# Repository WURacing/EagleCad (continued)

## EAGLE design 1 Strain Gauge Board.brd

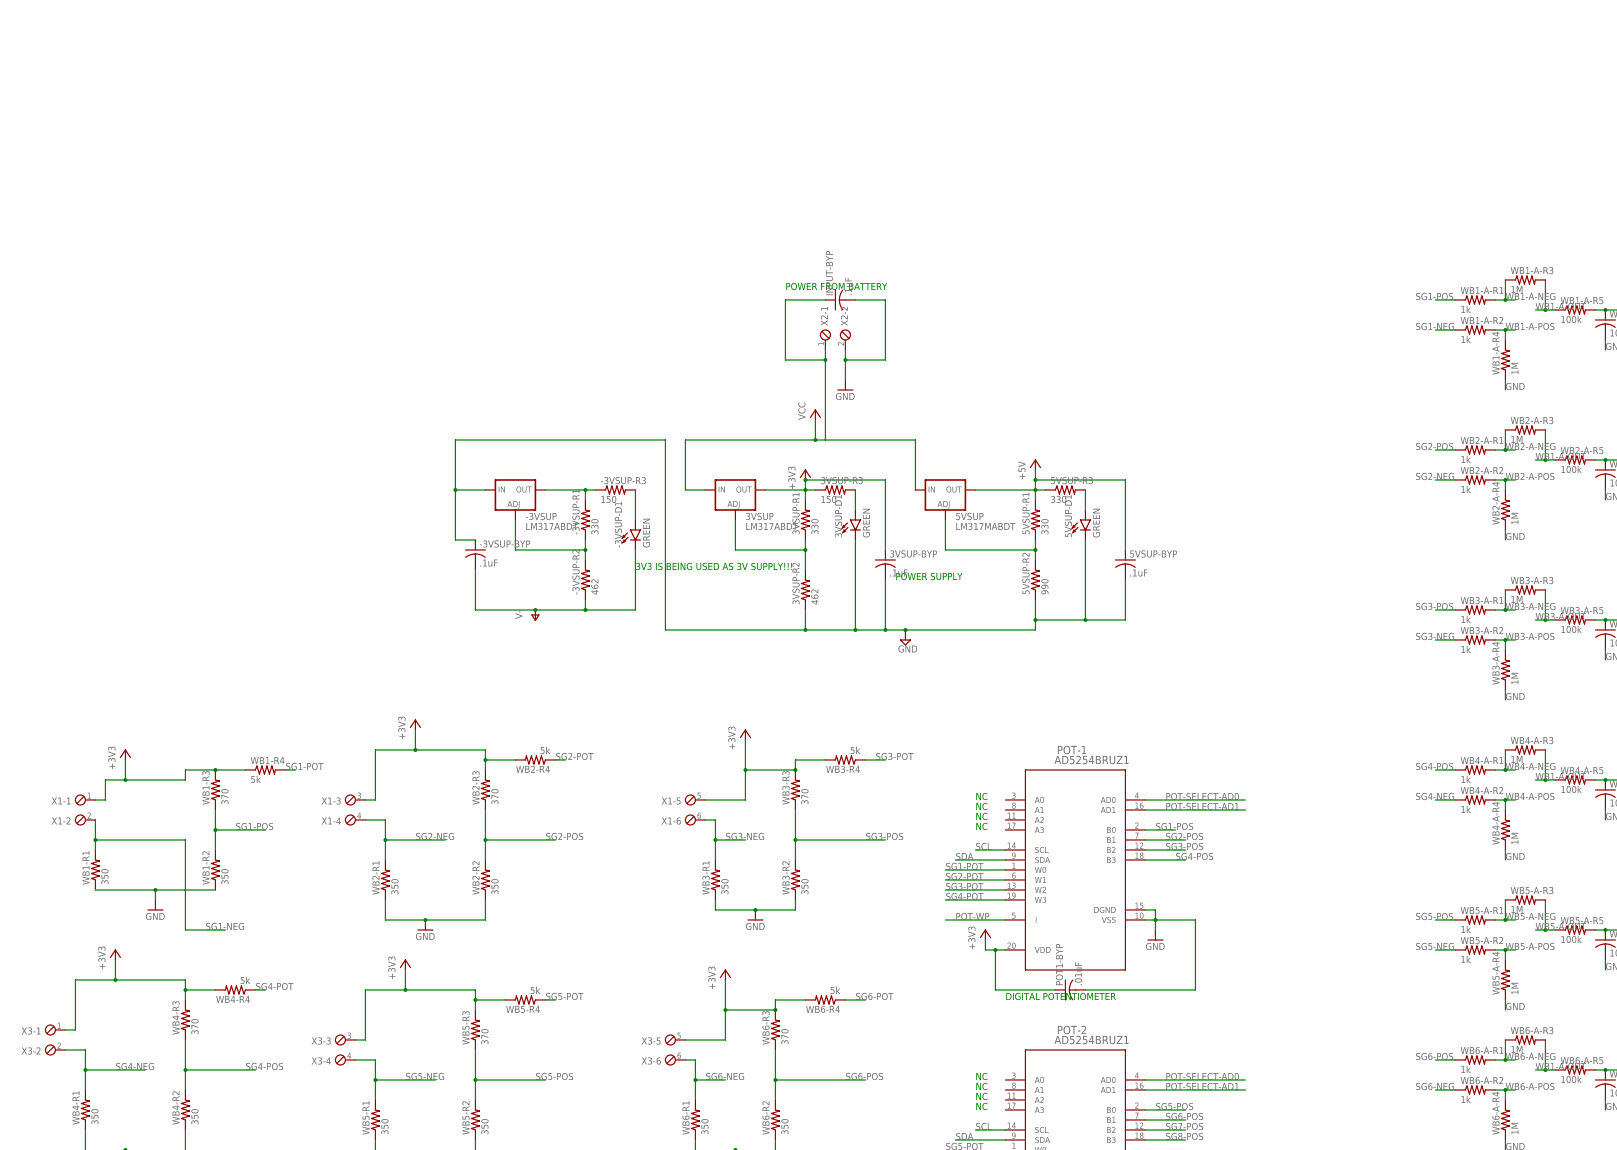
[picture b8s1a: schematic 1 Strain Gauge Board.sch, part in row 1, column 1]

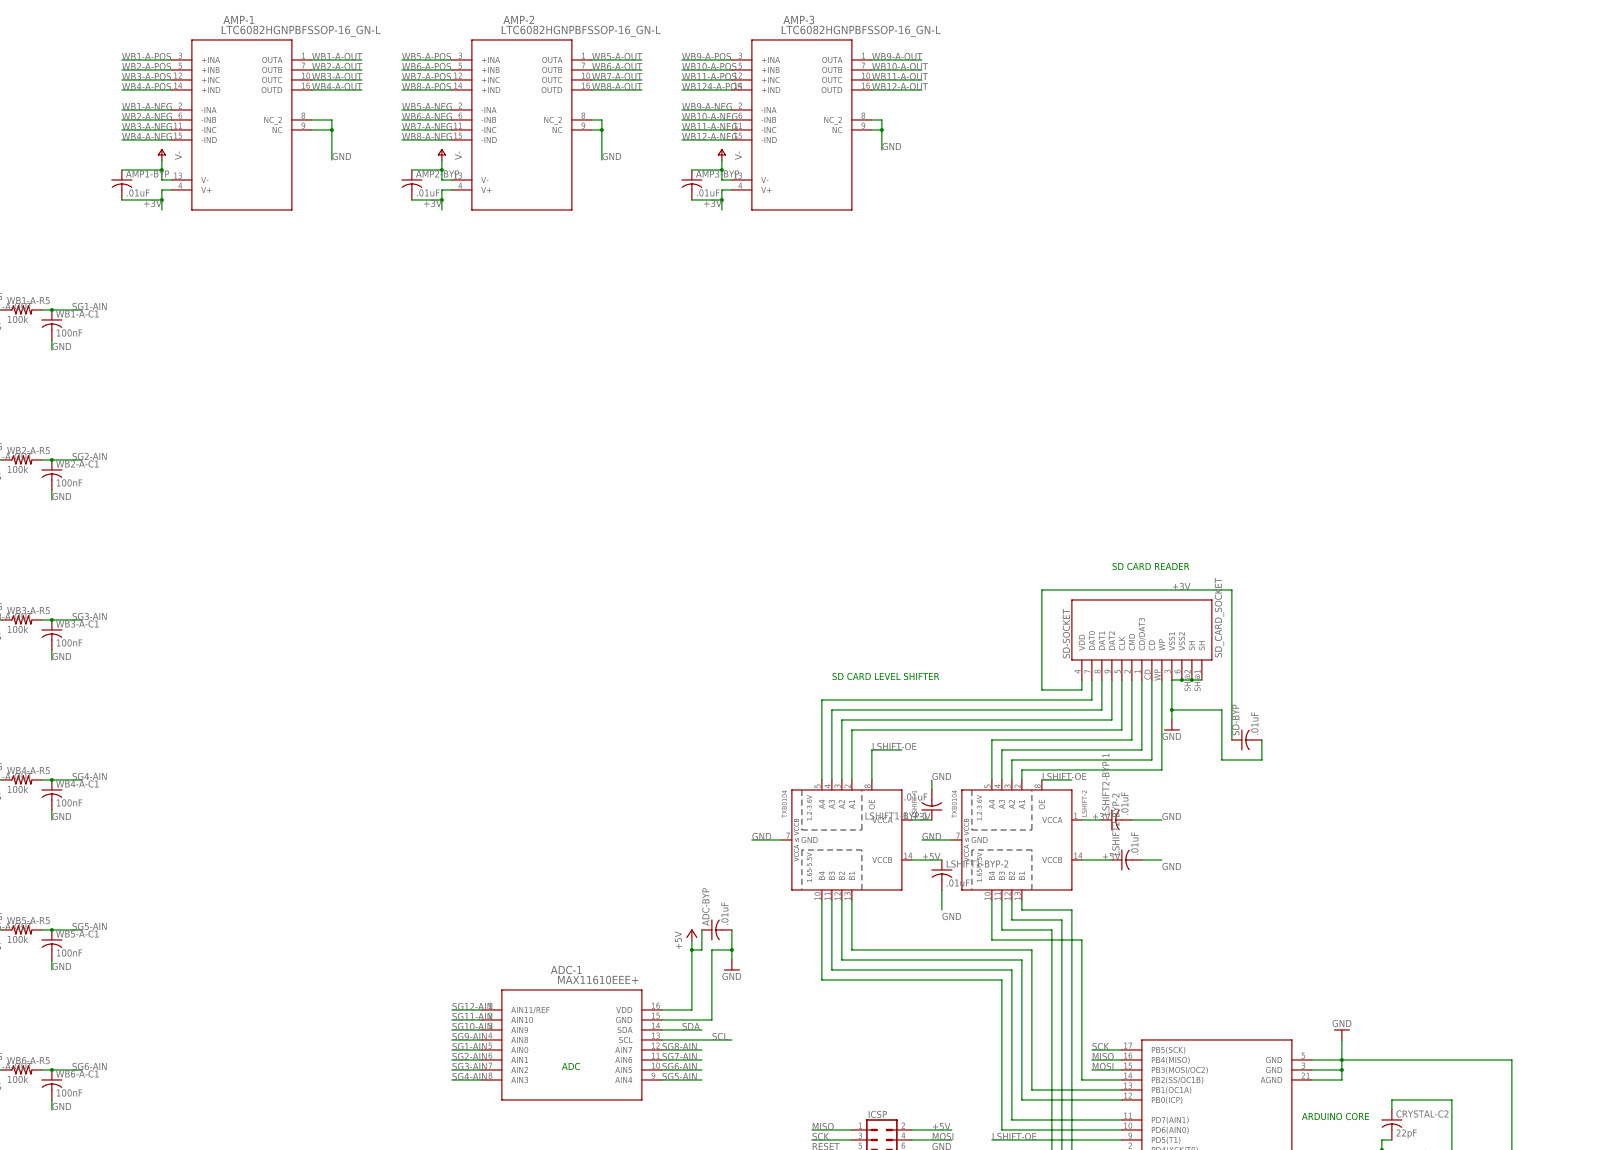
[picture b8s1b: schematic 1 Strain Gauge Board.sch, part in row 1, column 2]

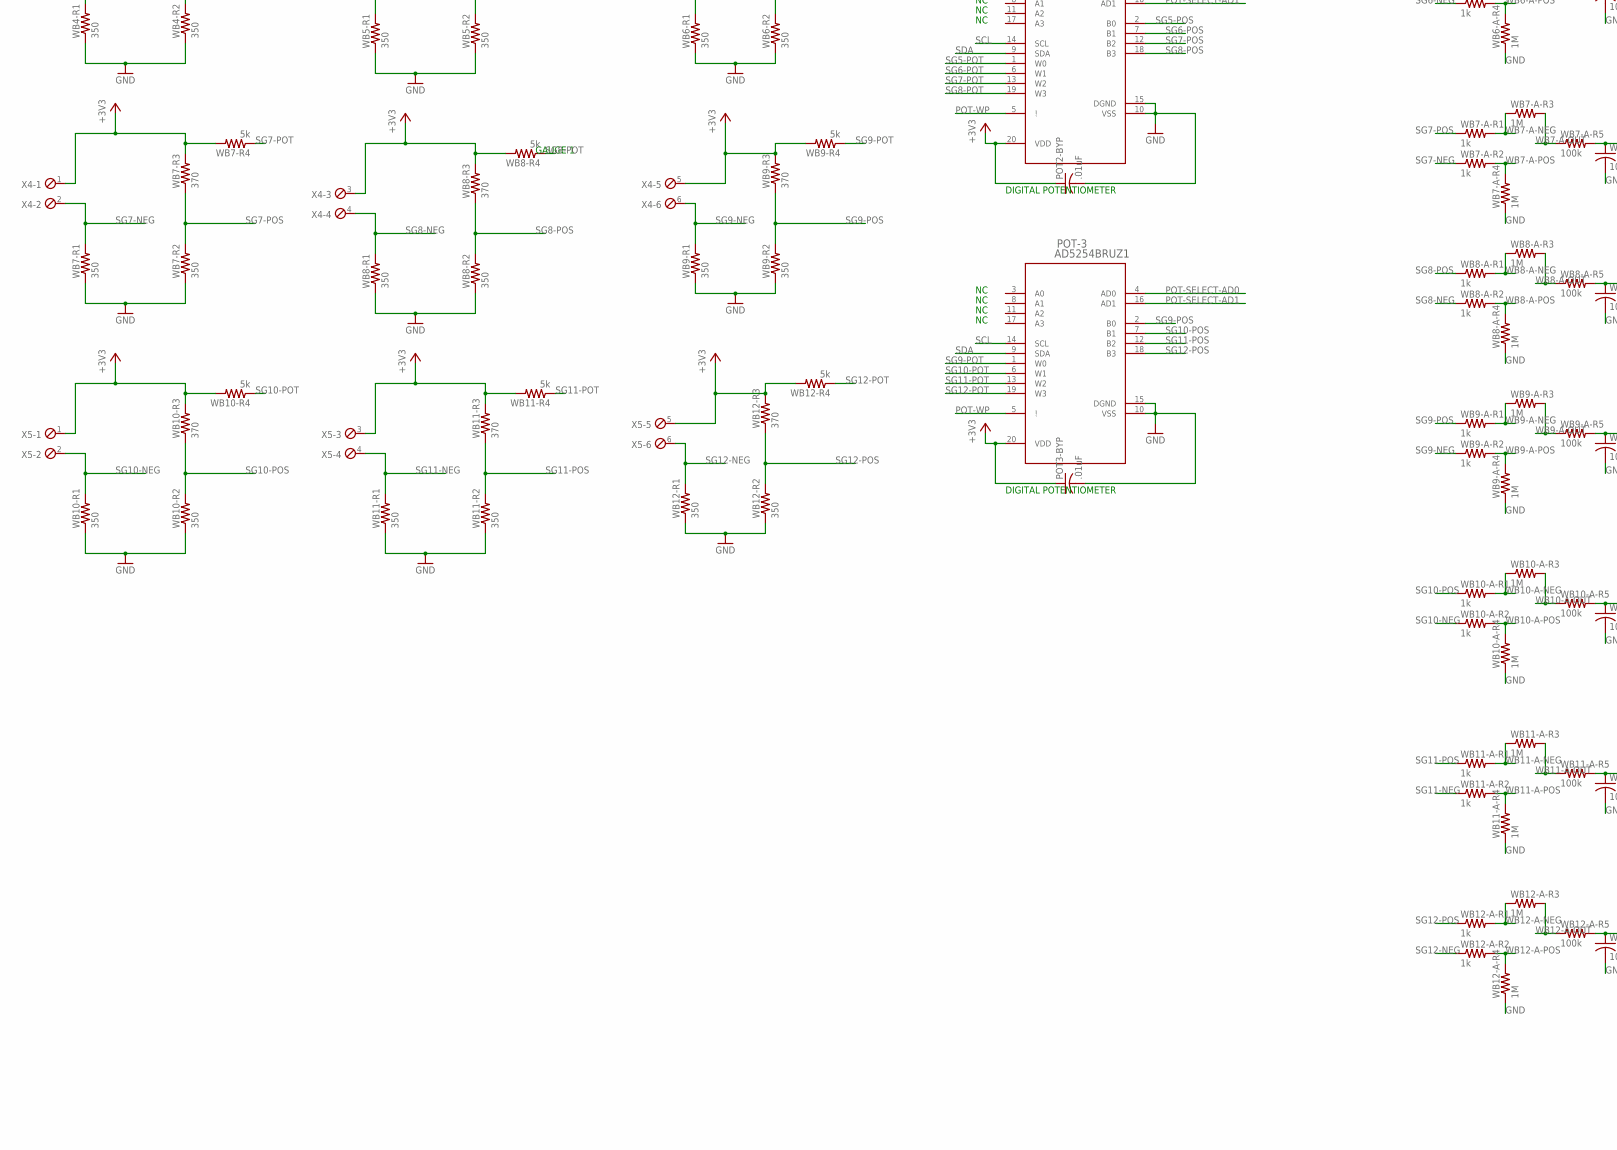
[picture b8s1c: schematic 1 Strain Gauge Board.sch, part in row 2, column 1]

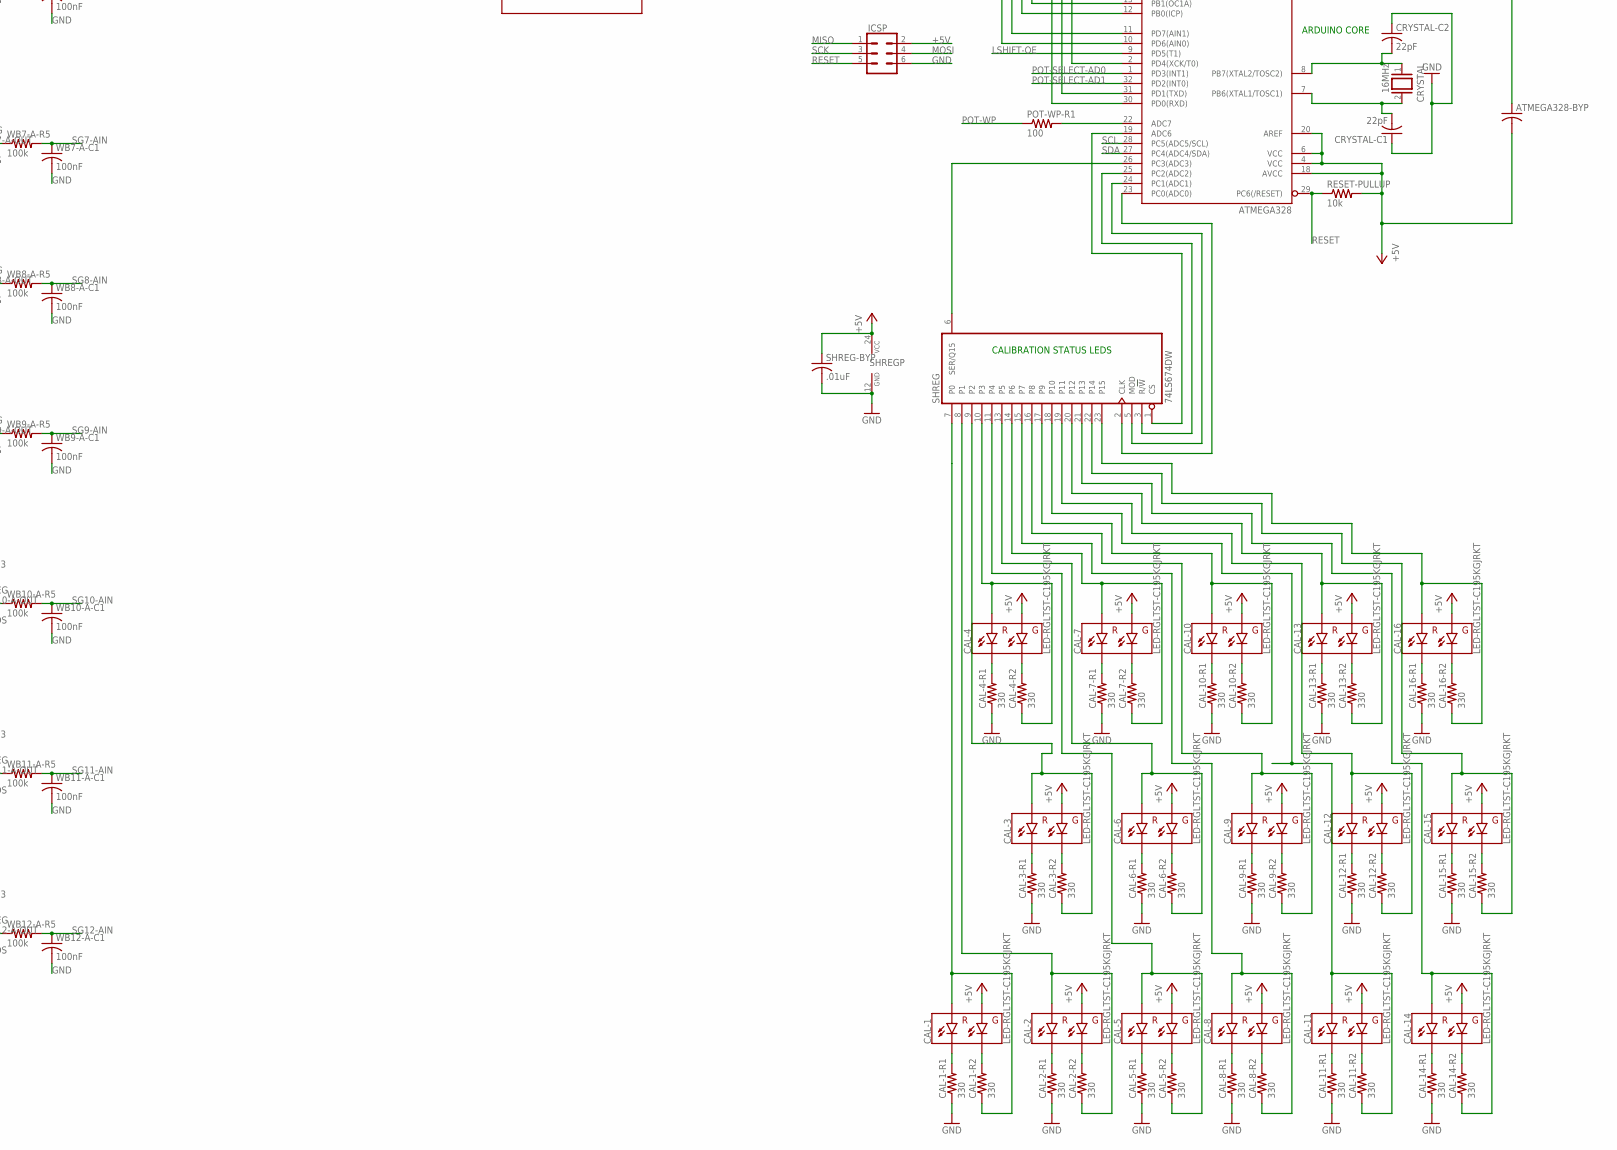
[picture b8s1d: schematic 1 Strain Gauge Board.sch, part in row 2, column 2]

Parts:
3VSUP: LM317ABDT; DPACK
3VSUP-BYP, 5VSUP-BYP: .1uF; C1206K
3VSUP-D1, 5VSUP-D1: GREEN; LED-1206
3VSUP-R1, 5VSUP-R1, 5VSUP-R3: 330; M1206
3VSUP-R2: 462; M1206
3VSUP-R3: 150; M1206
5VSUP: LM317MABDT; DPACK
5VSUP-R2: 990; M1206
-3VSUP: LM317ABDT; DPACK
-3VSUP-BYP: .1uF; C1206K
-3VSUP-D1: GREEN; LED-1206
-3VSUP-R1: 330; M1206
-3VSUP-R2: 462; M1206
-3VSUP-R3: 150; M1206
ADC-1: MAX11610EEE+; 21-0055H_16
ADC-BYP: .01uF; C1206K
AMP1-BYP, AMP2-BYP, AMP3-BYP: .01uF; C1206K
AMP-1, AMP-2, AMP-3: LTC6082HGNPBFSSOP-16_GN-L; SSOP-16_GN-L
ATMEGA328: ATMEGA328P_TQFP; TQFP32-08
ATMEGA328-BYP: C-USC1206; C1206
CAL-1, CAL-2, CAL-3, CAL-4, CAL-5, CAL-6, CAL-7, CAL-8, CAL-9, CAL-10, CAL-11, CAL-12, CAL-13, CAL-14, CAL-15, CAL-16: LED-RGLTST-C195KGJRKT; LTST-C195KGJRKT
CAL-1-R1, CAL-1-R2, CAL-2-R1, CAL-2-R2, CAL-3-R1, CAL-3-R2, CAL-4-R1, CAL-4-R2, CAL-5-R1, CAL-5-R2, CAL-6-R1, CAL-6-R2, CAL-7-R1, CAL-7-R2, CAL-8-R1, CAL-8-R2, CAL-9-R1, CAL-9-R2, CAL-10-R1, CAL-10-R2, CAL-11-R1, CAL-11-R2, CAL-12-R1, CAL-12-R2, CAL-13-R1, CAL-13-R2, CAL-14-R1, CAL-14-R2, CAL-15-R1, CAL-15-R2, CAL-16-R1, CAL-16-R2: 330; M1206
CRYSTAL: 16MHz; QS
CRYSTAL-C1, CRYSTAL-C2: 22pF; C1206K
ICSP: CONN_03X2FEMALE; 2X3
INPUT-BYP: .1uF; C1206K
LSHIFT1-BYP-1, LSHIFT1-BYP-2, LSHIFT2-BYP-1, LSHIFT2-BYP-2: .01uF; C1206K
LSHIFT-1, LSHIFT-2: TXB0104; SO14
POT1-BYP, POT2-BYP, POT3-BYP: .01uF; C1206K
POT-1, POT-2, POT-3: AD5254BRUZ1; RU_20
POT-WP-R1: 100; M1206
RESET-PULLUP: 10k; M1206
SD-BYP: .01uF; C1206K
SD-SOCKET: SD_CARD_SOCKET; SD
SHREG: 74LS674DW; SO24W
SHREG-BYP: .01uF; C1206K
WB1-A-C1, WB2-A-C1, WB3-A-C1, WB4-A-C1, WB5-A-C1, WB6-A-C1, WB7-A-C1, WB8-A-C1, WB9-A-C1, WB10-A-C1, WB11-A-C1, WB12-A-C1: 100nF; C1206K
WB1-A-R1, WB1-A-R2, WB2-A-R1, WB2-A-R2, WB3-A-R1, WB3-A-R2, WB4-A-R1, WB4-A-R2, WB5-A-R1, WB5-A-R2, WB6-A-R1, WB6-A-R2, WB7-A-R1, WB7-A-R2, WB8-A-R1, WB8-A-R2, WB9-A-R1, WB9-A-R2, WB10-A-R1, WB10-A-R2, WB11-A-R1, WB11-A-R2, WB12-A-R1, WB12-A-R2: 1k; M1206
WB1-A-R3, WB1-A-R4, WB2-A-R3, WB2-A-R4, WB3-A-R3, WB3-A-R4, WB4-A-R3, WB4-A-R4, WB5-A-R3, WB5-A-R4, WB6-A-R3, WB6-A-R4, WB7-A-R3, WB7-A-R4, WB8-A-R3, WB8-A-R4, WB9-A-R3, WB9-A-R4, WB10-A-R3, WB10-A-R4, WB11-A-R3, WB11-A-R4, WB12-A-R3, WB12-A-R4: 1M; M1206
WB1-A-R5, WB2-A-R5, WB3-A-R5, WB4-A-R5, WB5-A-R5, WB6-A-R5, WB7-A-R5, WB8-A-R5, WB9-A-R5, WB10-A-R5, WB11-A-R5, WB12-A-R5: 100k; M1206
WB1-R1, WB1-R2, WB2-R1, WB2-R2, WB3-R1, WB3-R2, WB4-R1, WB4-R2, WB5-R1, WB5-R2, WB6-R1, WB6-R2, WB7-R1, WB7-R2, WB8-R1, WB8-R2, WB9-R1, WB9-R2, WB10-R1, WB10-R2, WB11-R1, WB11-R2, WB12-R1, WB12-R2: 350; M1206
WB1-R3, WB2-R3, WB3-R3, WB4-R3, WB5-R3, WB6-R3, WB7-R3, WB8-R3, WB9-R3, WB10-R3, WB11-R3, WB12-R3: 370; M1206
WB1-R4, WB2-R4, WB3-R4, WB4-R4, WB5-R4, WB6-R4, WB7-R4, WB8-R4, WB9-R4, WB10-R4, WB11-R4, WB12-R4: 5k; M1206
X1, X3, X4, X5: MPT6; 6POL254
X2: MPT2; 2POL254

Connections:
+3V: 3VSUP.4 (OUT), 3VSUP-BYP.1, 3VSUP-R1.2, 3VSUP-R3.1, AMP1-BYP.2, AMP2-BYP.2, AMP3-BYP.2, AMP-1.4 (V+), AMP-2.4 (V+), AMP-3.4 (V+), LSHIFT1-BYP-1.1, LSHIFT2-BYP-1.1, LSHIFT-1.1 (VCCA), LSHIFT-2.1 (VCCA), POT1-BYP.1, POT2-BYP.1, POT3-BYP.1, POT-1.20 (VDD), POT-2.20 (VDD), POT-3.20 (VDD), SD-BYP.1, SD-SOCKET.4 (VDD), WB1-R3.2, WB1-R4.1, WB2-R3.2, WB2-R4.2, WB3-R3.2, WB3-R4.2, WB4-R3.2, WB4-R4.2, WB5-R3.2, WB5-R4.2, WB6-R3.2, WB6-R4.2, WB7-R3.2, WB7-R4.2, WB8-R3.2, WB8-R4.2, WB9-R3.2, WB9-R4.2, WB10-R3.2, WB10-R4.2, WB11-R3.2, WB11-R4.2, WB12-R3.2, WB12-R4.2, X1.1, X1.3, X1.5, X3.1, X3.3, X3.5, X4.1, X4.3, X4.5, X5.1, X5.3, X5.5
+5V: 5VSUP.4 (OUT), 5VSUP-BYP.1, 5VSUP-R1.2, 5VSUP-R3.1, ADC-1.16 (VDD), ADC-BYP.1, ATMEGA328.4 (VCC), ATMEGA328.6 (VCC), ATMEGA328.18 (AVCC), ATMEGA328.20 (AREF), ATMEGA328-BYP.2, CAL-1.P$1 (GA), CAL-2.P$1 (GA), CAL-3.P$1 (GA), CAL-4.P$1 (GA), CAL-5.P$1 (GA), CAL-6.P$1 (GA), CAL-7.P$1 (GA), CAL-8.P$1 (GA), CAL-9.P$1 (GA), CAL-10.P$1 (GA), CAL-11.P$1 (GA), CAL-12.P$1 (GA), CAL-13.P$1 (GA), CAL-14.P$1 (GA), CAL-15.P$1 (GA), CAL-16.P$1 (GA), ICSP.2, LSHIFT1-BYP-2.1, LSHIFT2-BYP-2.1, LSHIFT-1.14 (VCCB), LSHIFT-2.14 (VCCB), RESET-PULLUP.2, SHREG.24 (VCC), SHREG-BYP.1
-3V: -3VSUP.4 (OUT), -3VSUP-R1.2, -3VSUP-R3.1
GND: 3VSUP-BYP.2, 3VSUP-D1.C, 3VSUP-R2.1, 5VSUP-BYP.2, 5VSUP-D1.C, 5VSUP-R2.1, -3VSUP.3 (IN), -3VSUP-BYP.1, ADC-1.15 (GND), ADC-BYP.2, AMP-1.8 (NC_2), AMP-1.9 (NC), AMP-2.8 (NC_2), AMP-2.9 (NC), AMP-3.8 (NC_2), AMP-3.9 (NC), ATMEGA328.3 (GND), ATMEGA328.5 (GND), ATMEGA328.21 (AGND), ATMEGA328-BYP.1, CAL-1-R1.1, CAL-2-R1.1, CAL-3-R1.1, CAL-4-R1.1, CAL-5-R1.1, CAL-6-R1.1, CAL-7-R1.1, CAL-8-R1.1, CAL-9-R1.1, CAL-10-R1.1, CAL-11-R1.1, CAL-12-R1.1, CAL-13-R1.1, CAL-14-R1.1, CAL-15-R1.1, CAL-16-R1.1, CRYSTAL-C1.1, CRYSTAL-C2.1, ICSP.6, INPUT-BYP.2, LSHIFT1-BYP-1.2, LSHIFT1-BYP-2.2, LSHIFT2-BYP-1.2, LSHIFT2-BYP-2.2, LSHIFT-1.7 (GND), LSHIFT-2.7 (GND), POT1-BYP.2, POT2-BYP.2, POT3-BYP.2, POT-1.10 (VSS), POT-1.15 (DGND), POT-2.10 (VSS), POT-2.15 (DGND), POT-3.10 (VSS), POT-3.15 (DGND), SD-BYP.2, SD-SOCKET.3 (VSS1), SD-SOCKET.6 (VSS2), SD-SOCKET.SH@1 (SH), SD-SOCKET.SH@2 (SH), SHREG.12 (GND), SHREG-BYP.2, WB1-A-C1.2, WB1-A-R4.1, WB1-R1.1, WB1-R2.1, WB2-A-C1.2, WB2-A-R4.1, WB2-R1.1, WB2-R2.1, WB3-A-C1.2, WB3-A-R4.1, WB3-R1.1, WB3-R2.1, WB4-A-C1.2, WB4-A-R4.1, WB4-R1.1, WB4-R2.1, WB5-A-C1.2, WB5-A-R4.1, WB5-R1.1, WB5-R2.1, WB6-A-C1.2, WB6-A-R4.1, WB6-R1.1, WB6-R2.1, WB7-A-C1.2, WB7-A-R4.1, WB7-R1.1, WB7-R2.1, WB8-A-C1.2, WB8-A-R4.1, WB8-R1.1, WB8-R2.1, WB9-A-C1.2, WB9-A-R4.1, WB9-R1.1, WB9-R2.1, WB10-A-C1.2, WB10-A-R4.1, WB10-R1.1, WB10-R2.1, WB11-A-C1.2, WB11-A-R4.1, WB11-R1.1, WB11-R2.1, WB12-A-C1.2, WB12-A-R4.1, WB12-R1.1, WB12-R2.1, X2.2
LSHIFT-OE: ATMEGA328.9 (PD5(T1)), LSHIFT-1.8 (OE), LSHIFT-2.8 (OE)
MISO: ATMEGA328.16 (PB4(MISO)), ICSP.1
MOSI: ATMEGA328.15 (PB3(MOSI/OC2)), ICSP.4
unnamed: -3VSUP-D1.A, -3VSUP-R3.2
unnamed: -3VSUP.1 (ADJ), -3VSUP-R1.1, -3VSUP-R2.2
unnamed: ATMEGA328.22 (ADC7), POT-WP-R1.2
unnamed: 3VSUP.1 (ADJ), 3VSUP-R1.1, 3VSUP-R2.2
unnamed: LSHIFT-2.4 (A3), SD-SOCKET.1 (CD/DAT3)
unnamed: 5VSUP.1 (ADJ), 5VSUP-R1.1, 5VSUP-R2.2
unnamed: LSHIFT-2.2 (A1), SD-SOCKET.WP
unnamed: LSHIFT-2.3 (A2), SD-SOCKET.CD
unnamed: LSHIFT-2.5 (A4), SD-SOCKET.2 (CMD)
unnamed: ATMEGA328.7 (PB6(XTAL1/TOSC1)), CRYSTAL.2, CRYSTAL-C1.2
unnamed: ATMEGA328.8 (PB7(XTAL2/TOSC2)), CRYSTAL.1, CRYSTAL-C2.2
unnamed: LSHIFT-1.2 (A1), SD-SOCKET.5 (CLK)
unnamed: LSHIFT-1.3 (A2), SD-SOCKET.9 (DAT2)
unnamed: LSHIFT-1.4 (A3), SD-SOCKET.8 (DAT1)
unnamed: LSHIFT-1.5 (A4), SD-SOCKET.7 (DAT0)
unnamed: CAL-1.P$4 (RC), CAL-1-R1.2
unnamed: CAL-1.P$3 (GC), CAL-1-R2.2
unnamed: CAL-1.P$2 (RA), CAL-1-R2.1, SHREG.7 (P0)
unnamed: ATMEGA328.2 (PD4(XCK/T0)), LSHIFT-2.13 (B1)
unnamed: ATMEGA328.31 (PD1(TXD)), LSHIFT-2.12 (B2)
unnamed: ATMEGA328.30 (PD0(RXD)), LSHIFT-2.11 (B3)
unnamed: ATMEGA328.14 (PB2(SS/OC1B)), LSHIFT-2.10 (B4)
unnamed: ATMEGA328.13 (PB1(OC1A)), LSHIFT-1.13 (B1)
unnamed: ATMEGA328.12 (PB0(ICP)), LSHIFT-1.12 (B2)
unnamed: ATMEGA328.11 (PD7(AIN1)), LSHIFT-1.11 (B3)
unnamed: ATMEGA328.10 (PD6(AIN0)), LSHIFT-1.10 (B4)
unnamed: ATMEGA328.26 (PC3(ADC3)), SHREG.6 (SER/Q15)
unnamed: ATMEGA328.23 (PC0(ADC0)), SHREG.2 (CLK)
unnamed: ATMEGA328.24 (PC1(ADC1)), SHREG.5 (MOD)
unnamed: ATMEGA328.25 (PC2(ADC2)), SHREG.3 (R/!W)
unnamed: ATMEGA328.19 (ADC6), SHREG.1 (CS)
unnamed: CAL-2.P$4 (RC), CAL-2-R1.2
unnamed: CAL-2.P$3 (GC), CAL-2-R2.2
unnamed: 3VSUP-D1.A, 3VSUP-R3.2
unnamed: 5VSUP-D1.A, 5VSUP-R3.2
unnamed: CAL-2.P$2 (RA), CAL-2-R2.1, SHREG.8 (P1)
unnamed: CAL-5.P$4 (RC), CAL-5-R1.2
unnamed: CAL-5.P$3 (GC), CAL-5-R2.2
unnamed: CAL-5.P$2 (RA), CAL-5-R2.1, SHREG.11 (P4)
unnamed: CAL-8.P$4 (RC), CAL-8-R1.2
unnamed: CAL-8.P$3 (GC), CAL-8-R2.2
unnamed: CAL-8.P$2 (RA), CAL-8-R2.1, SHREG.15 (P7)
unnamed: CAL-6.P$4 (RC), CAL-6-R1.2
unnamed: CAL-6.P$3 (GC), CAL-6-R2.2
unnamed: CAL-6.P$2 (RA), CAL-6-R2.1, SHREG.13 (P5)
unnamed: CAL-3.P$4 (RC), CAL-3-R1.2
unnamed: CAL-3.P$3 (GC), CAL-3-R2.2
unnamed: CAL-3.P$2 (RA), CAL-3-R2.1, SHREG.9 (P2)
unnamed: CAL-9.P$4 (RC), CAL-9-R1.2
unnamed: CAL-9.P$3 (GC), CAL-9-R2.2
unnamed: CAL-9.P$2 (RA), CAL-9-R2.1, SHREG.16 (P8)
unnamed: CAL-11.P$4 (RC), CAL-11-R1.2
unnamed: CAL-11.P$3 (GC), CAL-11-R2.2
unnamed: CAL-11.P$2 (RA), CAL-11-R2.1, SHREG.18 (P10)
unnamed: CAL-12.P$4 (RC), CAL-12-R1.2
unnamed: CAL-12.P$3 (GC), CAL-12-R2.2
unnamed: CAL-12.P$2 (RA), CAL-12-R2.1, SHREG.19 (P11)
unnamed: CAL-14.P$4 (RC), CAL-14-R1.2
unnamed: CAL-14.P$3 (GC), CAL-14-R2.2
unnamed: CAL-14.P$2 (RA), CAL-14-R2.1, SHREG.21 (P13)
unnamed: CAL-15.P$4 (RC), CAL-15-R1.2
unnamed: CAL-15.P$3 (GC), CAL-15-R2.2
unnamed: CAL-15.P$2 (RA), CAL-15-R2.1, SHREG.22 (P14)
unnamed: CAL-7.P$4 (RC), CAL-7-R1.2
unnamed: CAL-7.P$3 (GC), CAL-7-R2.2
unnamed: CAL-7.P$2 (RA), CAL-7-R2.1, SHREG.14 (P6)
unnamed: CAL-10.P$4 (RC), CAL-10-R1.2
unnamed: CAL-10.P$3 (GC), CAL-10-R2.2
unnamed: CAL-10.P$2 (RA), CAL-10-R2.1, SHREG.17 (P9)
unnamed: CAL-13.P$4 (RC), CAL-13-R1.2
unnamed: CAL-13.P$3 (GC), CAL-13-R2.2
unnamed: CAL-13.P$2 (RA), CAL-13-R2.1, SHREG.20 (P12)
unnamed: CAL-16.P$4 (RC), CAL-16-R1.2
unnamed: CAL-16.P$3 (GC), CAL-16-R2.2
unnamed: CAL-16.P$2 (RA), CAL-16-R2.1, SHREG.23 (P15)
unnamed: CAL-4.P$4 (RC), CAL-4-R1.2
unnamed: CAL-4.P$3 (GC), CAL-4-R2.2
unnamed: CAL-4.P$2 (RA), CAL-4-R2.1, SHREG.10 (P3)
POT-SELECT-AD0: ATMEGA328.1 (PD3(INT1)), POT-1.4 (AD0), POT-2.4 (AD0), POT-3.4 (AD0)
POT-SELECT-AD1: ATMEGA328.32 (PD2(INT0)), POT-1.16 (AD1), POT-2.16 (AD1), POT-3.16 (AD1)
POT-WP: POT-1.5 (!), POT-2.5 (!), POT-3.5 (!), POT-WP-R1.1
RESET: ATMEGA328.29 (PC6(/RESET)), ICSP.5, RESET-PULLUP.1
SCK: ATMEGA328.17 (PB5(SCK)), ICSP.3
SCL: ADC-1.13 (SCL), ATMEGA328.28 (PC5(ADC5/SCL)), POT-1.14 (SCL), POT-2.14 (SCL), POT-3.14 (SCL)
SDA: ADC-1.14 (SDA), ATMEGA328.27 (PC4(ADC4/SDA)), POT-1.9 (SDA), POT-2.9 (SDA), POT-3.9 (SDA)
SG1-AIN: ADC-1.5 (AIN0), WB1-A-C1.1, WB1-A-R5.2
SG1-NEG: WB1-A-R2.1, WB1-R1.2, X1.2
SG1-POS: POT-1.2 (B0), WB1-A-R1.1, WB1-R2.2, WB1-R3.1
SG1-POT: POT-1.1 (W0), WB1-R4.2
SG2-AIN: ADC-1.6 (AIN1), WB2-A-C1.1, WB2-A-R5.2
SG2-NEG: WB2-A-R2.1, WB2-R1.2, X1.4
SG2-POS: POT-1.7 (B1), WB2-A-R1.1, WB2-R2.2, WB2-R3.1
SG2-POT: POT-1.6 (W1), WB2-R4.1
SG3-AIN: ADC-1.7 (AIN2), WB3-A-C1.1, WB3-A-R5.2
SG3-NEG: WB3-A-R2.1, WB3-R1.2, X1.6
SG3-POS: POT-1.12 (B2), WB3-A-R1.1, WB3-R2.2, WB3-R3.1
SG3-POT: POT-1.13 (W2), WB3-R4.1
SG4-AIN: ADC-1.8 (AIN3), WB4-A-C1.1, WB4-A-R5.2
SG4-NEG: WB4-A-R2.1, WB4-R1.2, X3.2
SG4-POS: POT-1.18 (B3), WB4-A-R1.1, WB4-R2.2, WB4-R3.1
SG4-POT: POT-1.19 (W3), WB4-R4.1
SG5-AIN: ADC-1.9 (AIN4), WB5-A-C1.1, WB5-A-R5.2
SG5-NEG: WB5-A-R2.1, WB5-R1.2, X3.4
SG5-POS: POT-2.2 (B0), WB5-A-R1.1, WB5-R2.2, WB5-R3.1
SG5-POT: POT-2.1 (W0), WB5-R4.1
SG6-AIN: ADC-1.10 (AIN5), WB6-A-C1.1, WB6-A-R5.2
SG6-NEG: WB6-A-R2.1, WB6-R1.2, X3.6
SG6-POS: POT-2.7 (B1), WB6-A-R1.1, WB6-R2.2, WB6-R3.1
SG6-POT: POT-2.6 (W1), WB6-R4.1
SG7-AIN: ADC-1.11 (AIN6), WB7-A-C1.1, WB7-A-R5.2
SG7-NEG: WB7-A-R2.1, WB7-R1.2, X4.2
SG7-POS: POT-2.12 (B2), WB7-A-R1.1, WB7-R2.2, WB7-R3.1
SG7-POT: POT-2.13 (W2), WB7-R4.1
SG8-AIN: ADC-1.12 (AIN7), WB8-A-C1.1, WB8-A-R5.2
SG8-NEG: WB8-A-R2.1, WB8-R1.2, X4.4
SG8-POS: POT-2.18 (B3), WB8-A-R1.1, WB8-R2.2, WB8-R3.1
SG8-POT: POT-2.19 (W3), WB8-R4.1
SG9-AIN: ADC-1.4 (AIN8), WB9-A-C1.1, WB9-A-R5.2
SG9-NEG: WB9-A-R2.1, WB9-R1.2, X4.6
SG9-POS: POT-3.2 (B0), WB9-A-R1.1, WB9-R2.2, WB9-R3.1
SG9-POT: POT-3.1 (W0), WB9-R4.1
SG10-AIN: ADC-1.3 (AIN9), WB10-A-C1.1, WB10-A-R5.2
SG10-NEG: WB10-A-R2.1, WB10-R1.2, X5.2
SG10-POS: POT-3.7 (B1), WB10-A-R1.1, WB10-R2.2, WB10-R3.1
SG10-POT: POT-3.6 (W1), WB10-R4.1
SG11-AIN: ADC-1.2 (AIN10), WB11-A-C1.1, WB11-A-R5.2
SG11-NEG: WB11-A-R2.1, WB11-R1.2, X5.4
SG11-POS: POT-3.12 (B2), WB11-A-R1.1, WB11-R2.2, WB11-R3.1
SG11-POT: POT-3.13 (W2), WB11-R4.1
SG12-AIN: ADC-1.1 (AIN11/REF), WB12-A-C1.1, WB12-A-R5.2
SG12-NEG: WB12-A-R2.1, WB12-R1.2, X5.6
SG12-POS: POT-3.18 (B3), WB12-A-R1.1, WB12-R2.2, WB12-R3.1
SG12-POT: POT-3.19 (W3), WB12-R4.1
V-: -3VSUP-BYP.2, -3VSUP-D1.C, -3VSUP-R2.1, AMP1-BYP.1, AMP2-BYP.1, AMP3-BYP.1, AMP-1.13 (V-), AMP-2.13 (V-), AMP-3.13 (V-)
VCC: 3VSUP.3 (IN), 5VSUP.3 (IN), INPUT-BYP.1, X2.1
WB1-A-NEG: AMP-1.2 (-INA), WB1-A-R1.2, WB1-A-R3.1
WB1-A-OUT: AMP-1.1 (OUTA), WB1-A-R3.2, WB1-A-R5.1, WB2-A-R3.2, WB2-A-R5.1, WB4-A-R3.2, WB4-A-R5.1, WB6-A-R3.2, WB6-A-R5.1
WB1-A-POS: AMP-1.3 (+INA), WB1-A-R2.2, WB1-A-R4.2
WB2-A-NEG: AMP-1.6 (-INB), WB2-A-R1.2, WB2-A-R3.1
WB2-A-OUT: AMP-1.7 (OUTB)
WB2-A-POS: AMP-1.5 (+INB), WB2-A-R2.2, WB2-A-R4.2
WB3-A-NEG: AMP-1.11 (-INC), WB3-A-R1.2, WB3-A-R3.1
WB3-A-OUT: AMP-1.10 (OUTC), WB3-A-R3.2, WB3-A-R5.1
WB3-A-POS: AMP-1.12 (+INC), WB3-A-R2.2, WB3-A-R4.2
WB4-A-NEG: AMP-1.15 (-IND), WB4-A-R1.2, WB4-A-R3.1
WB4-A-OUT: AMP-1.16 (OUTD)
WB4-A-POS: AMP-1.14 (+IND), WB4-A-R2.2, WB4-A-R4.2
WB5-A-NEG: AMP-2.2 (-INA), WB5-A-R1.2, WB5-A-R3.1
WB5-A-OUT: AMP-2.1 (OUTA), WB5-A-R3.2, WB5-A-R5.1
WB5-A-POS: AMP-2.3 (+INA), WB5-A-R2.2, WB5-A-R4.2
WB6-A-NEG: AMP-2.6 (-INB), WB6-A-R1.2, WB6-A-R3.1
WB6-A-OUT: AMP-2.7 (OUTB)
WB6-A-POS: AMP-2.5 (+INB), WB6-A-R2.2, WB6-A-R4.2
WB7-A-NEG: AMP-2.11 (-INC), WB7-A-R1.2, WB7-A-R3.1
WB7-A-OUT: AMP-2.10 (OUTC), WB7-A-R3.2, WB7-A-R5.1
WB7-A-POS: AMP-2.12 (+INC), WB7-A-R2.2, WB7-A-R4.2
WB8-A-NEG: AMP-2.15 (-IND), WB8-A-R1.2, WB8-A-R3.1
WB8-A-OUT: AMP-2.16 (OUTD), WB8-A-R3.2, WB8-A-R5.1
WB8-A-POS: AMP-2.14 (+IND), WB8-A-R2.2, WB8-A-R4.2
WB9-A-NEG: AMP-3.2 (-INA), WB9-A-R1.2, WB9-A-R3.1
WB9-A-OUT: AMP-3.1 (OUTA), WB9-A-R3.2, WB9-A-R5.1
WB9-A-POS: AMP-3.3 (+INA), WB9-A-R2.2, WB9-A-R4.2
WB10-A-NEG: AMP-3.6 (-INB), WB10-A-R1.2, WB10-A-R3.1
WB10-A-OUT: AMP-3.7 (OUTB), WB10-A-R3.2, WB10-A-R5.1
WB10-A-POS: AMP-3.5 (+INB), WB10-A-R2.2, WB10-A-R4.2
WB11-A-NEG: AMP-3.11 (-INC), WB11-A-R1.2, WB11-A-R3.1
WB11-A-OUT: AMP-3.10 (OUTC), WB11-A-R3.2, WB11-A-R5.1
WB11-A-POS: AMP-3.12 (+INC), WB11-A-R2.2, WB11-A-R4.2
WB12-A-NEG: AMP-3.15 (-IND), WB12-A-R1.2, WB12-A-R3.1
WB12-A-OUT: AMP-3.16 (OUTD), WB12-A-R3.2, WB12-A-R5.1
WB12-A-POS: WB12-A-R2.2, WB12-A-R4.2
WB124-A-POS: AMP-3.14 (+IND)

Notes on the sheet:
GAUGE 1
3V3 IS BEING USED AS 3V SUPPLY!!!
POWER FROM BATTERY
CALIBRATION STATUS LEDS
ADC
DIGITAL POTENTIOMETER
POWER SUPPLY
SD CARD LEVEL SHIFTER
SD CARD READER
ARDUINO CORE

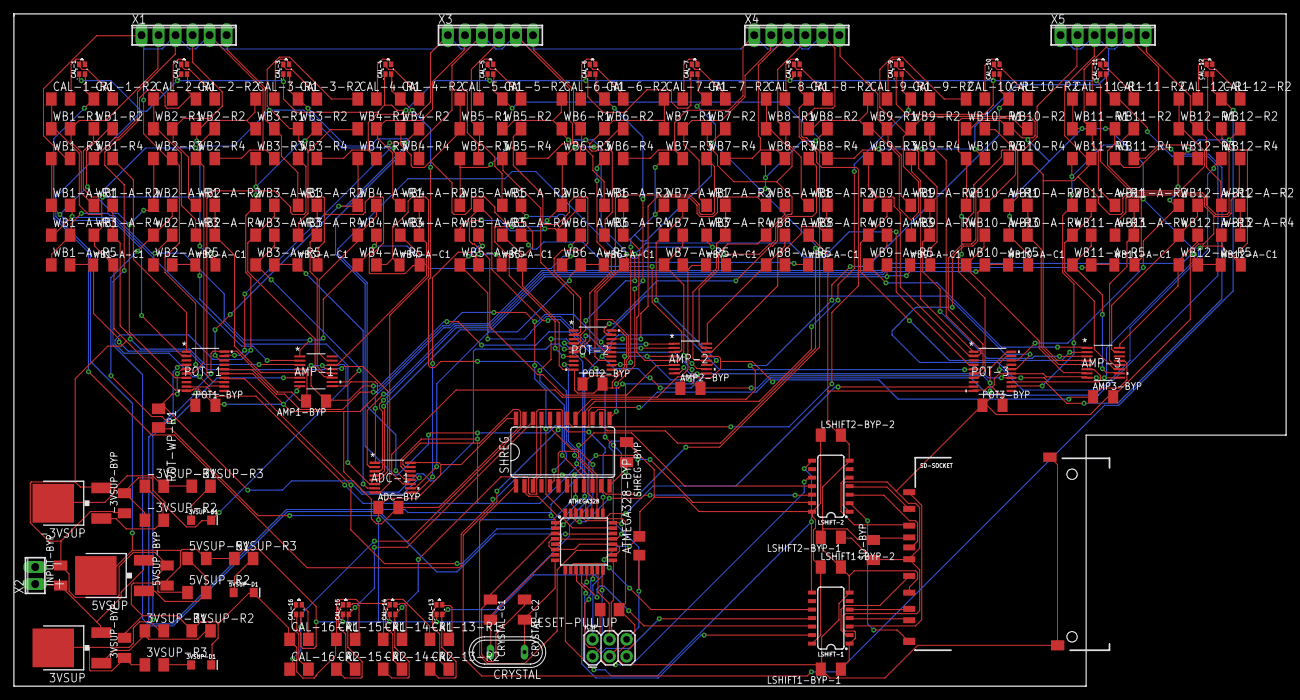
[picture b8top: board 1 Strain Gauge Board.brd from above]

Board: 2 copper layers, 189.9 x 100.3 mm, 224 parts (0 on the bottom side), 175 nets.

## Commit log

2016-09-10 Added EagleCad Projects Dashboard and CanController
2016-09-10 Added schematic files
2016-09-10 Added Wiring Harness Schemaic
2016-10-22 revision 1 for dashboard shield pcb
2017-09-09 added can shield used in 2016-2017 season
2017-09-20 Add new attiny CAN communicator
2017-10-22 Add CAN communiator for ATmega328P
2017-10-31 Update drawing
2017-11-01 Credit myself
2017-11-03 Add actual mounting holes
    2M clearance
2017-11-04 Move programming header to the side
2017-11-04 Move digital pin 6 to 11 (4 to 5)
2017-11-04 Credit Ethan
2018-01-20 Redesign PCB slightly
2018-03-03 addition of brake light PCB design
2018-04-07 Switched to a simpler design
2018-04-14 Added author name to board
2018-09-12 Added design for Strain Gauge
    Rev 0.5: Design supports (most) of a 1 strain gauge or 1/3 rosette gauge reader/store
    MISSING: programming header
2018-09-13 Version 1 FINAL
    Nearly complete version of the first iteration of the strain gauge logger.
    TODO: Check SD card for validity. I have no idea how it's supposed to be hooked up.
2018-09-19 New board with updated ADC1256 from TI
    TODO: Redo calibration circuitry to be single-pot per bridge (REMOVE 1 pot chip), and add in 370 and 5k resistors as done in previous board versions
    TODO: Add in programming header, SD card reader, and voltage regulators.
2018-09-19 Version 2_UPDATED_ADC
    Added in voltage regulators, power and programming headers, and bypass capacitors
    TODO: Still need to add in SD card reader circuitry.
    CHECK: Do we need to set AGND on the ADC to the sensor ground? Is the 0.5V regulator going to produce a steady reference voltage? What is the voltage for the strain gauges (UPDATE R2 VALUE WHEN WE KN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
2018-09-19 Added SD Card reader
    TODO: Verify if we need to use 3V3 or 5V for the SD card. If it's 3V, then we need to add in a level shifter between ATMEGA and the card.
2018-09-19 Added SD Card
    Forgot to add bypass cap to the SD card reader
2018-09-19 Fixed ERC
    Went through ERC and fixed/approved all errors/warnings except for continuity ones. Board needs to be redrawn completely
2018-09-21 Version 2 Board File
    Added in board file. FINAL
2018-09-21 ERC Compliant
2018-09-21 Size and DRC Optimizations
    Final size: 1.5"x2.5". Might be a little tricky to solder now, but oh well
2018-09-21 Optimized size and solderability
2018-09-24 Backlink to CADLAB.io has been added.
2018-09-25 Full scale board design
2018-09-25 Routed board
    Not optimized for size. This is a POC to get an idea of what the minimum size of the board can be
2018-09-25 First size optimization
    3.75x2.5 down to 3.5x2.5
2018-09-25 Size optimization round 2
    Down to 3.1x2.5
2018-09-25 Size optimization V3
    THERE IS A MISSING CONNECTION! THIS IS ONLY A PROGRESS UPDATE
2018-09-25 Converted to 4 layer board
    Down to 2.3x2.7
2018-09-25 4 Layer Size Optimization 2
    Now 2.4x2.3
2018-09-25 Fixed wheatstone bridges
    forgot a resistor on bridge
2018-09-26 Added in R3 to bridges
    2.4x2.8"
2018-09-29 Add files via upload
    First design of the 2019 brake light using 1206 SMD LEDs
2018-10-04 Ground plane
    Maybe this will be finished. Maybe it won't.
2018-10-04 ADD MORE GROUND PLANE
    update: board wasn't finished
2018-10-05 More ground plane + silkscreen readability
    Still not done yet...
2018-10-05 Finished silkscreen cleanup
    Looks readable now, still need to add WURACING logo
2018-10-05 MOAR GROUND PLANE
    added more ground plane area
2018-10-05 ... more ground plane, anyone?
    Still need to correctly import the .bmp image
2018-10-11 Start redesign
2018-10-12 Before SD fix
2018-10-13 Readability, and made board smaller (again)
    Schematic: Moved things around to make it more easily read
    Board: Moved things around to shrink the board and increase the ground plane area
2018-10-17 Optimized wire routing
2018-10-25 Full bridge board
    Initial revision
2018-10-25 Increased power trace width
2018-10-25 Let the optimizing begin...
2018-10-28 Ground plane, readability, trace length, yadda yadda yadda
2018-10-28 Readability and other small changes
2018-11-27 Teensy shield version
2018-11-29 Make the battery face the right way
2019-01-15 Add files via upload
    changed out LEDs and voltage regulator for better ones.
2019-01-19 Add files via upload
    Here you go tony
2019-01-19 WIP datalogger
2019-01-26 Add files via upload
    Changed LED configuration and removed 5V capability
2019-01-26 Add files via upload
    Unfucked the Ground and Power planes
2019-01-26 Add files via upload
    Changed to Molex connector
2019-01-26 Make board
2019-01-26 Updated mounting hole locations and board size
    Probably final version
2019-01-26 More work
2019-01-28 Add USB-C and PRGM button
2019-01-29 Add files via upload
    Changed resistor values
2019-02-06 Add files via upload
    Brakelight is done!
2019-02-09 Add SAM communicator
2019-02-09 CAN sensor data ingestion
2019-02-10 Add files via upload
    Changed the sizes & positions of the holes on the board
2019-02-11 Add pullup on SWDCLK and RC filter on RESET_L
2019-02-11 Fix resistor placement by connector, mask vias
2019-02-19 Move some signal traces away from capacitors
2019-02-19 Make ground plane better cover some analog inputs
2019-02-19 added power plane
2019-02-23 moved some decoupling caps
2019-02-23 First iteration of CAN datalogger using diode RTC
2019-03-08 Diode-less battery RTC with external IC
2019-03-09 Fix insanely obvious error in CAN interface
    VSS means GROUND, VDD means POWER
2019-03-09 I'm an idiot
2019-04-03 moved some stuff
2019-04-04 connected ground planes
2019-04-04 fixed DRC errors
2019-04-04 Revert changes in sensor.brd
    The file in this branch is out of date and will break when we try
    to merge otherwise.
2019-04-23 Take out the trash
